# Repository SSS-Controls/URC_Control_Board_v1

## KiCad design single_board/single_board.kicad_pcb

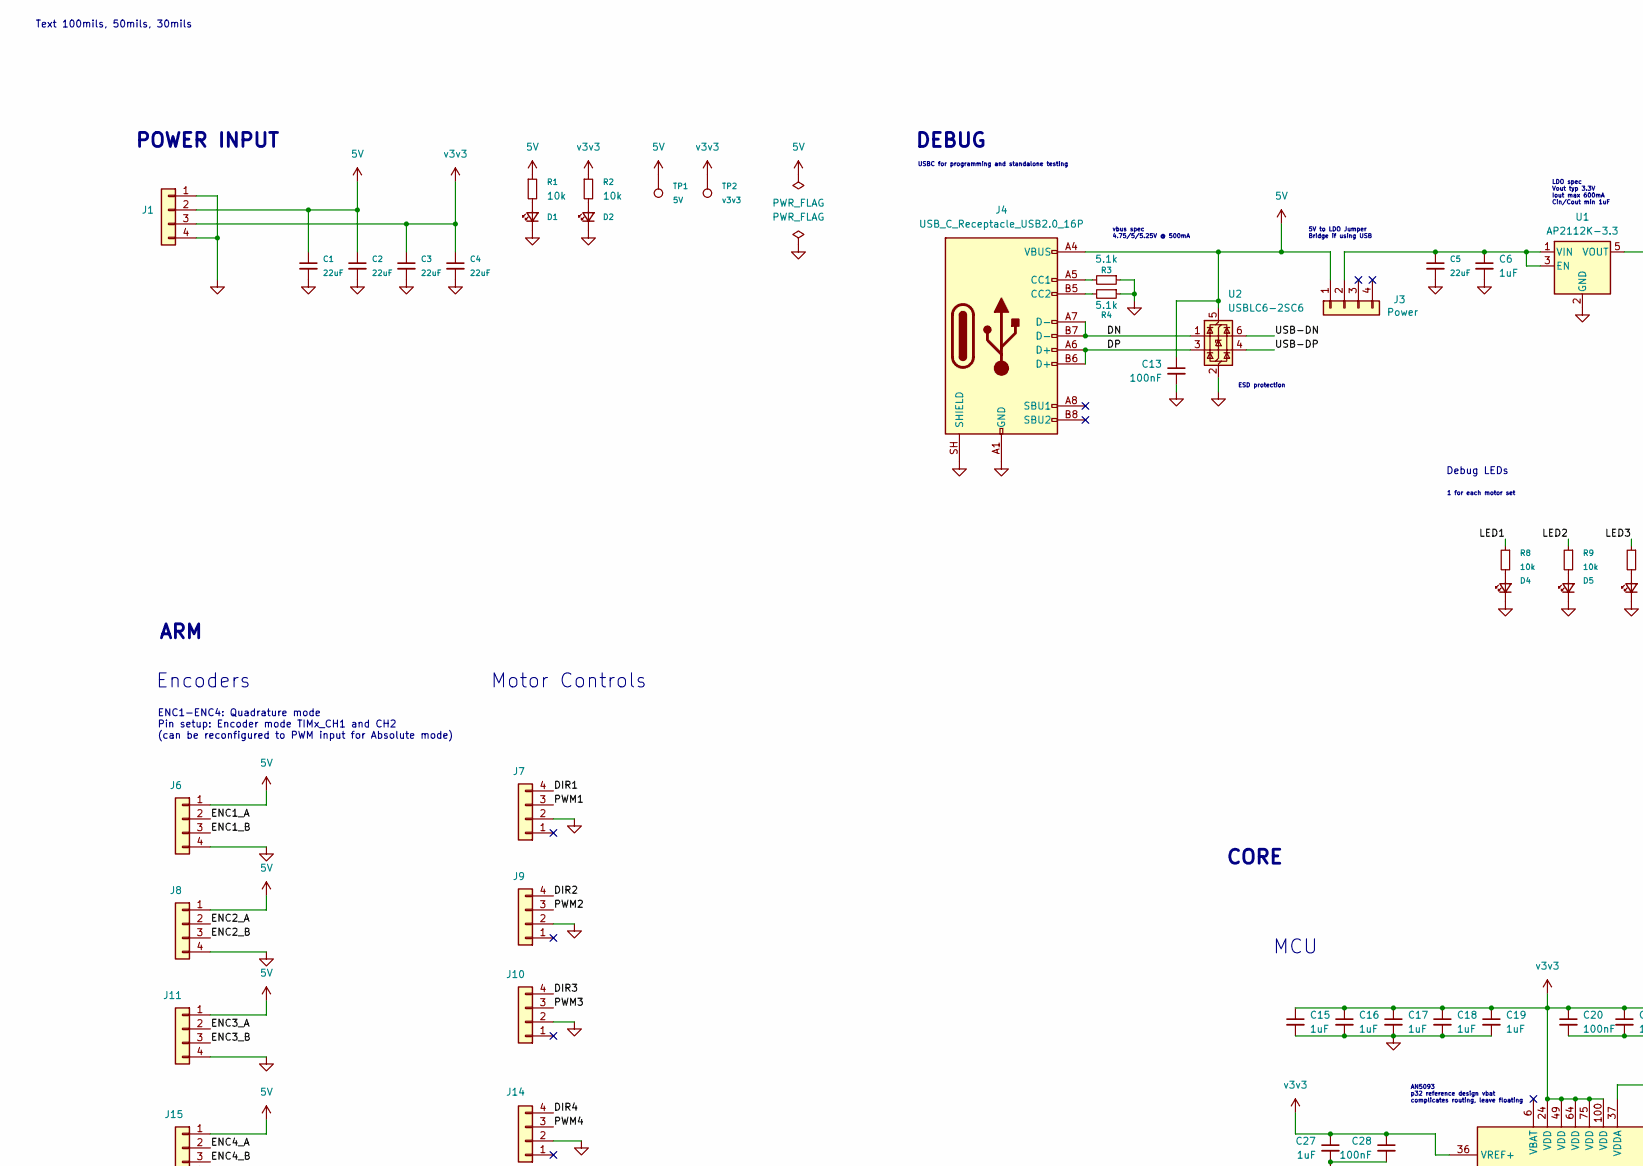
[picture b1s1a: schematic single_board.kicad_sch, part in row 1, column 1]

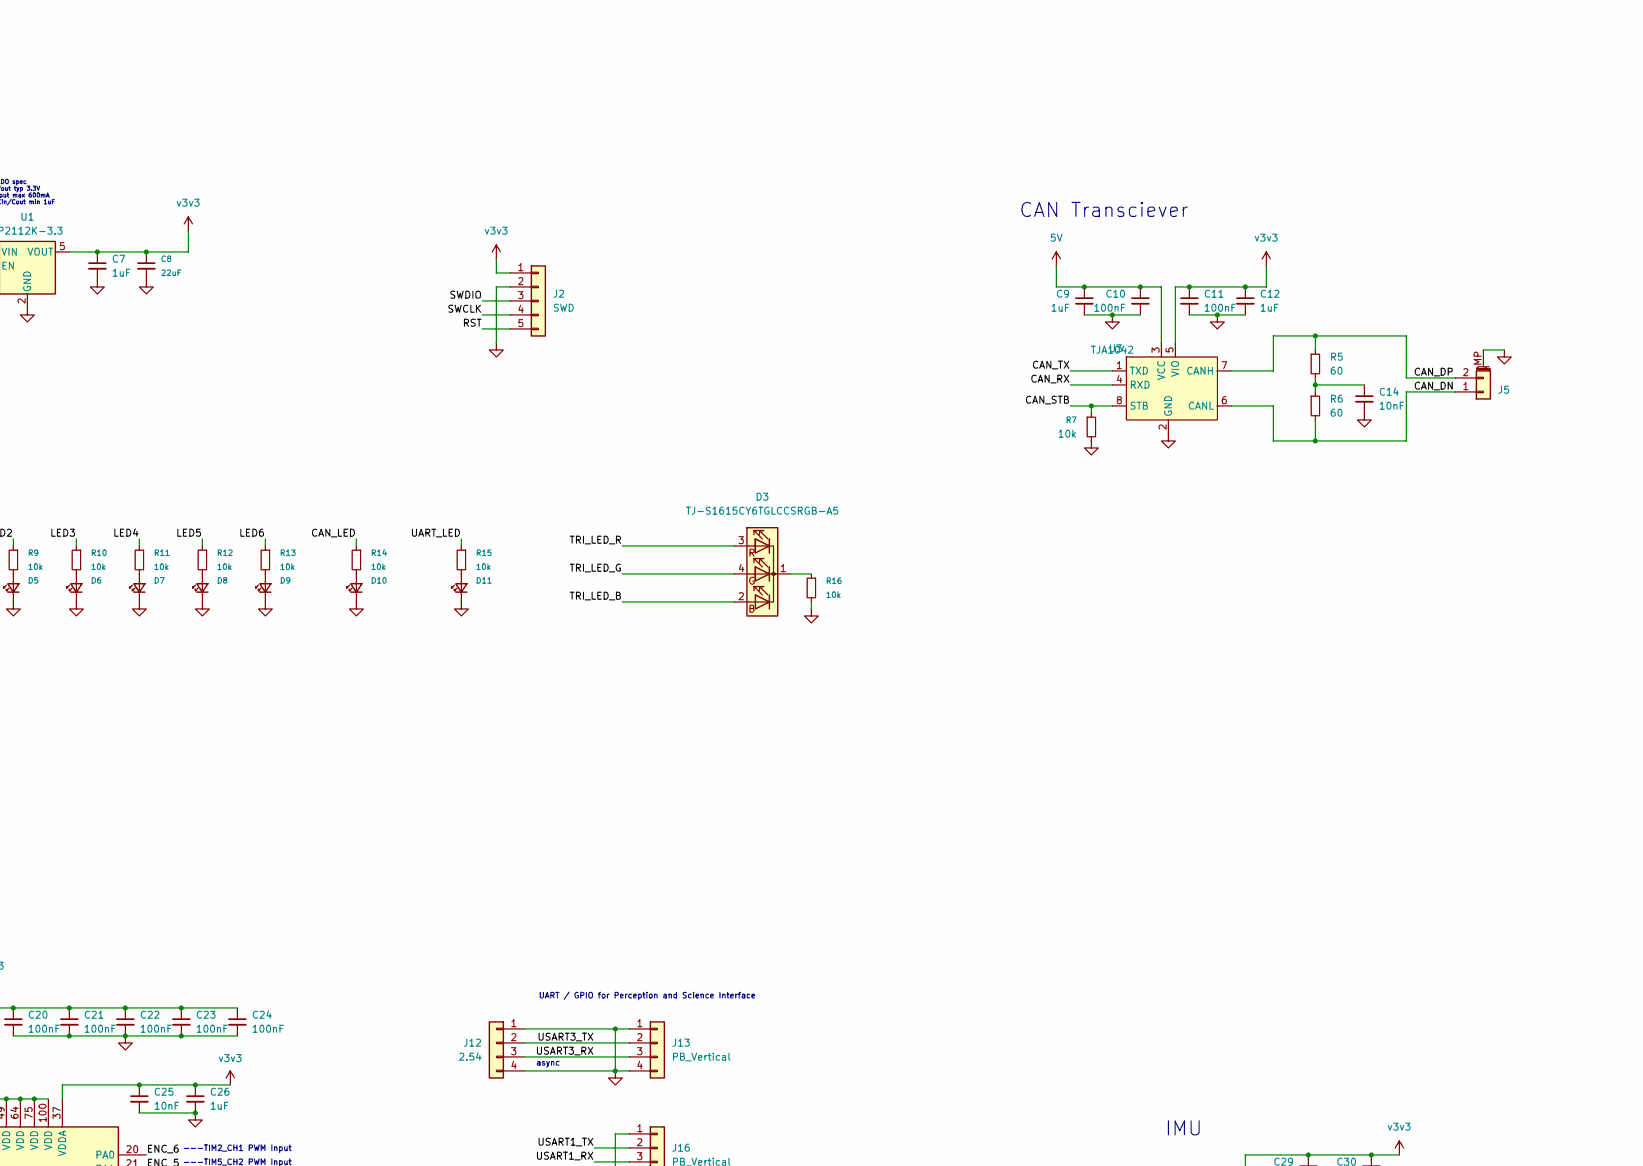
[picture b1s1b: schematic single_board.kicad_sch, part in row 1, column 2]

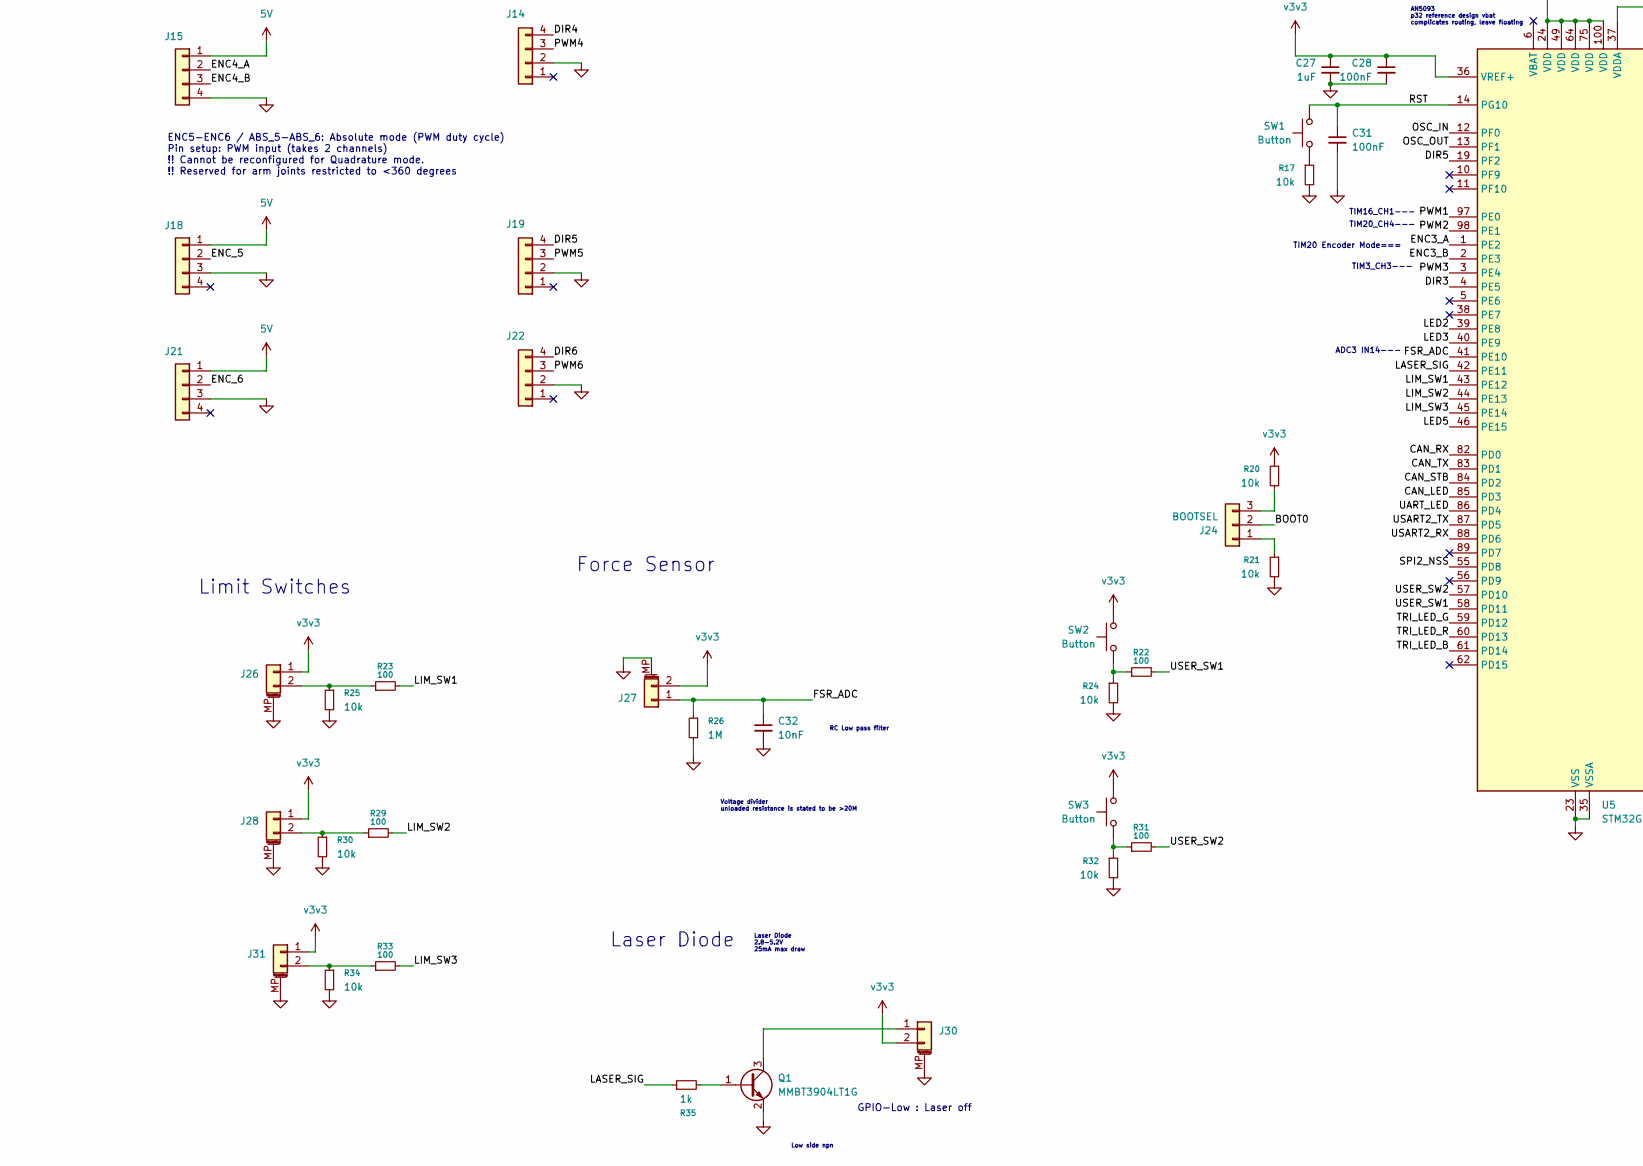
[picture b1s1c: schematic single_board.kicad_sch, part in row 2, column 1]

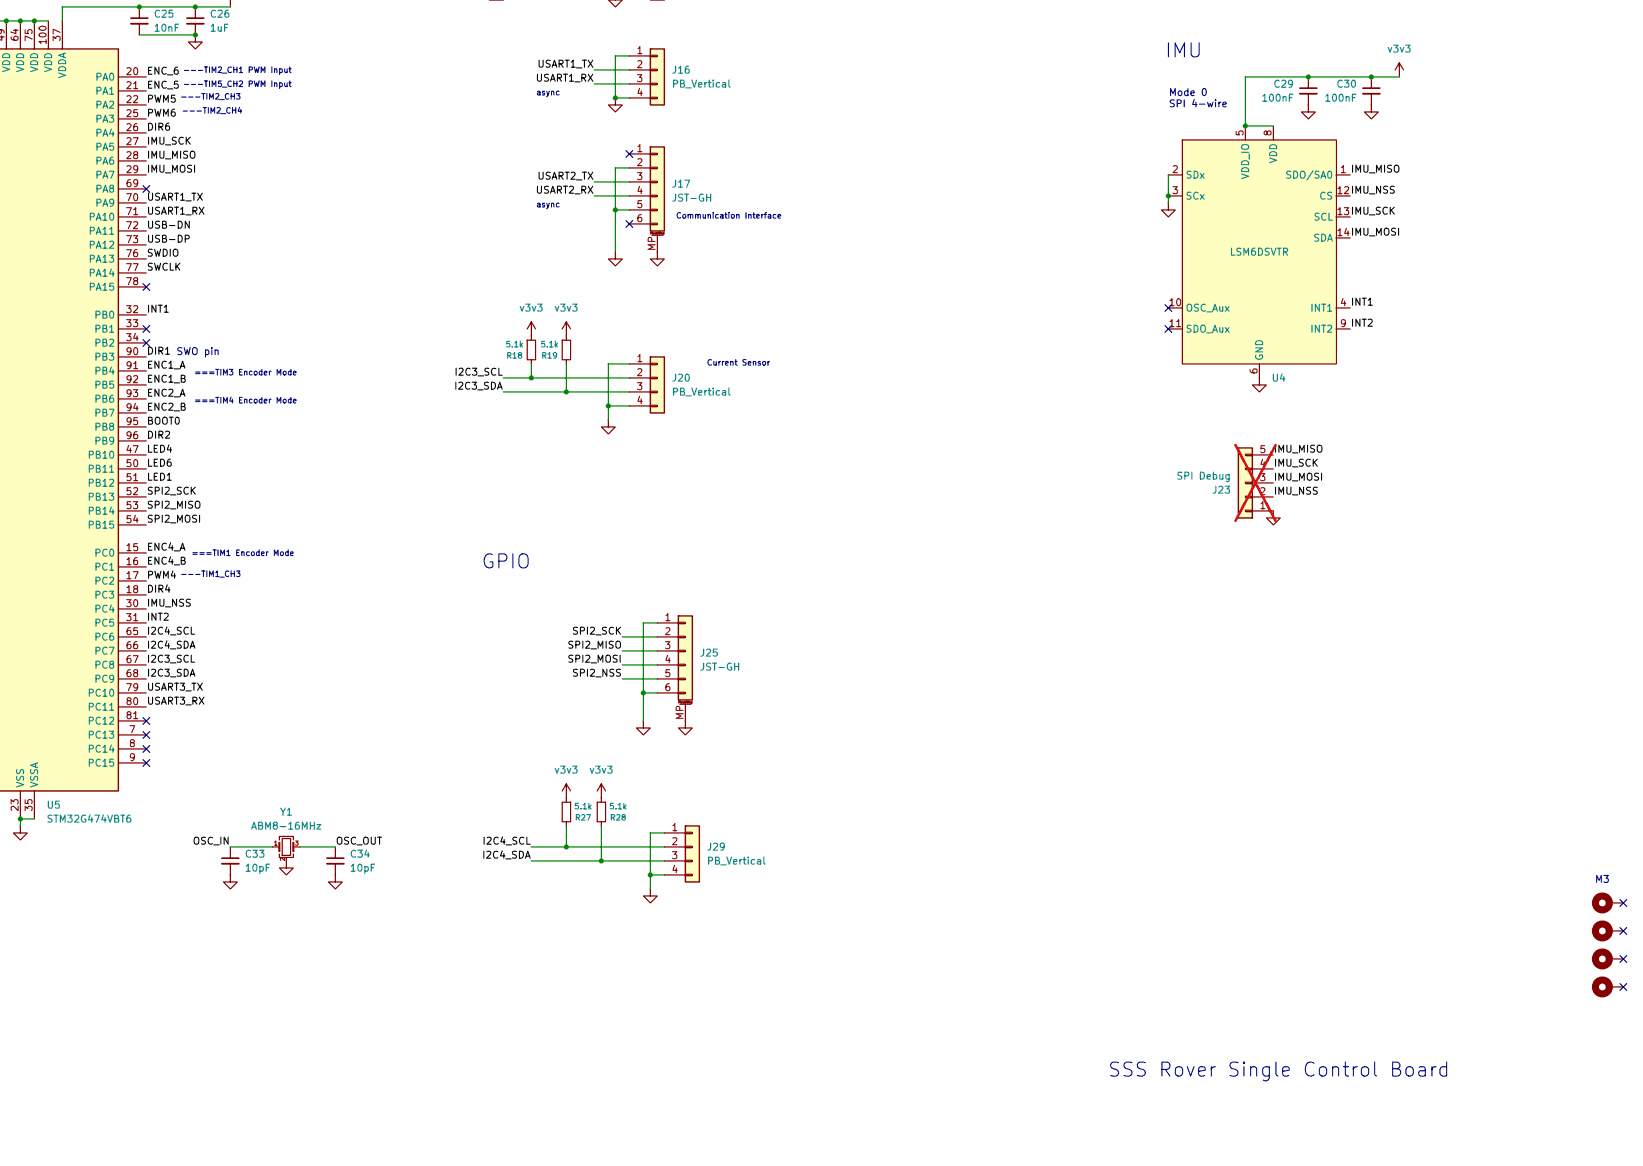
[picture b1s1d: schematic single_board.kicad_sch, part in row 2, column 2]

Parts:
C1, C2, C3, C4, C5, C8: 22uF; C_0805_2012Metric; LCSC Part # C602037
C6, C7, C9, C12, C15, C16, C17, C18, C19, C26, C27: 1uF; C_0402_1005Metric; LCSC Part # C52923
C10, C11, C13, C20, C21, C22, C23, C24, C28, C29, C30, C31: 100nF; C_0402_1005Metric; LCSC Part # C100072
C14, C25, C32: 10nF; C_0402_1005Metric; LCSC Part # C15195
C33, C34: 10pF; C_0402_1005Metric; LCSC Part # C76946
D1, D2: LED_Small; LED_0603_1608Metric; LCSC Part # C5160697
D3: TJ-S1615CY6TGLCCSRGB-A5; TOGAILED; LCSC Part # C601684
D4, D5, D6, D7, D8, D9, D10, D11: LED; LED_0603_1608Metric; LCSC Part # C5160697
H1, H2, H3, H4: M3; MountingHole_3.2mm_M3_Pad
J1, J6, J7, J8, J9, J10, J11, J13, J14, J15, J16, J18, J19, J20, J21, J22, J29: PB_Vertical; Molex_PicoBlade_53047-0410_1x04_P1.25mm_Vertical; LCSC Part # C504989
J2: SWD; PinHeader_1x05_P2.54mm_Vertical
J3: Power; PinHeader_1x04_P2.54mm_Vertical
J4: USB_C_Receptacle_USB2.0_16P; USB_C_Receptacle_HRO_TYPE-C-31-M-12; LCSC Part # C165948
J5, J26, J27, J28, J30, J31: JST_GH; JST_GH_SM02B-GHS-TB_1x02-1MP_P1.25mm_Horizontal; LCSC Part # C189893
J12: 2.54; 2.54 SMD
J17, J25: JST-GH; JST_GH_SM06B-GHS-TB_1x06-1MP_P1.25mm_Horizontal; LCSC Part # C133065
J23: SPI Debug; PinHeader_1x05_P1.27mm_Vertical; not fitted
J24: BOOTSEL; PinHeader_1x03_P2.54mm_Vertical
Q1: MMBT3904LT1G; SOT-23; LCSC Part # C81464
R1, R2, R7, R8, R9, R10, R11, R12, R13, R14, R15, R16, R17, R20, R21, R24, R25, R30, R32, R34: 10k; R_0402_1005Metric; LCSC Part # C71617
R3, R4, R18, R19, R27, R28: 5.1k; R_0402_1005Metric; LCSC Part # C105872
R5, R6: 60; R_0402_1005Metric; LCSC Part # C416565
R22, R23, R29, R31, R33: 100; R_0402_1005Metric; LCSC Part # C413063
R26: 1M; R_0402_1005Metric; LCSC Part # C26083
R35: 1k; R_0402_1005Metric
SW1, SW2, SW3: Button; SW_SPST_PTS810; LCSC Part # C221897
TP1: 5V; TestPoint_Pad_D1.5mm
TP2: v3v3; TestPoint_Pad_D1.5mm
U1: AP2112K-3.3; SOT-23-5; LCSC Part # C51118
U2: USBLC6-2SC6; SOT-23-6; LCSC Part # C7519
U3: TJA1042; SOIC-8_3.9x4.9mm_P1.27mm; LCSC Part # C53670
U4: LSM6DSVTR; LSM6DSV; LCSC Part # C5267399
U5: STM32G474VBT6; LQFP-100_14x14mm_P0.5mm; LCSC Part # C730130
Y1: ABM8-16MHz; Crystal_SMD_Abracon_ABM8G-4Pin_3.2x2.5mm; LCSC Part # C179641

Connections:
5V: C1.1, C2.1, C9.1, C10.1, C13.1, J1.2, J3.1, J4.A4 (VBUS), J4.A9 (VBUS), J4.B4 (VBUS), J4.B9 (VBUS), J6.1, J8.1, J11.1, J15.1, J18.1, J21.1, R1.1, TP1.1 (1_1), U2.5 (VBUS), U3.3 (VCC)
/BOOT0: J24.2, U5.95 (PB8)
/CAN_DN: J5.1, R6.2, U3.6 (CANL)
/CAN_DP: J5.2, R5.1, U3.7 (CANH)
/CAN_LED: R14.1, U5.85 (PD3)
/CAN_RX: U3.4 (RXD), U5.82 (PD0)
/CAN_STB: R7.1, U3.8 (STB), U5.84 (PD2)
/CAN_TX: U3.1 (TXD), U5.83 (PD1)
/DIR1: J7.4, U5.90 (PB3)
/DIR2: J9.4, U5.96 (PB9)
/DIR3: J10.4, U5.4 (PE5)
/DIR4: J14.4, U5.18 (PC3)
/DIR5: J19.4, U5.19 (PF2)
/DIR6: J22.4, U5.26 (PA4)
/DN: J4.A7 (D-), J4.B7 (D-), U2.1 (I/O1)
/DP: J4.A6 (D+), J4.B6 (D+), U2.3 (I/O2)
/ENC1_A: J6.2, U5.91 (PB4)
/ENC1_B: J6.3, U5.92 (PB5)
/ENC2_A: J8.2, U5.93 (PB6)
/ENC2_B: J8.3, U5.94 (PB7)
/ENC3_A: J11.2, U5.1 (PE2)
/ENC3_B: J11.3, U5.2 (PE3)
/ENC4_A: J15.2, U5.15 (PC0)
/ENC4_B: J15.3, U5.16 (PC1)
/ENC_5: J18.2, U5.21 (PA1)
/ENC_6: J21.2, U5.20 (PA0)
/FSR_ADC: C32.1, J27.1, R26.1, U5.41 (PE10)
/I2C3_SCL: J20.2, R18.2, U5.67 (PC8)
/I2C3_SDA: J20.3, R19.2, U5.68 (PC9)
/I2C4_SCL: J29.2, R27.2, U5.65 (PC6)
/I2C4_SDA: J29.3, R28.2, U5.66 (PC7)
/IMU_MISO: J23.5, U4.1 (SDO/SA0), U5.28 (PA6)
/IMU_MOSI: J23.3, U4.14 (SDA), U5.29 (PA7)
/IMU_NSS: J23.2, U4.12 (CS), U5.30 (PC4)
/IMU_SCK: J23.4, U4.13 (SCL), U5.27 (PA5)
/INT1: U4.4 (INT1), U5.32 (PB0)
/INT2: U4.9 (INT2), U5.31 (PC5)
/LASER_SIG: R35.1, U5.42 (PE11)
/LED1: R8.1, U5.51 (PB12)
/LED2: R9.1, U5.39 (PE8)
/LED3: R10.1, U5.40 (PE9)
/LED4: R11.1, U5.47 (PB10)
/LED5: R12.1, U5.46 (PE15)
/LED6: R13.1, U5.50 (PB11)
/LIM_SW1: R23.2, U5.43 (PE12)
/LIM_SW2: R29.2, U5.44 (PE13)
/LIM_SW3: R33.2, U5.45 (PE14)
/OSC_IN: C33.1, U5.12 (PF0), Y1.1
/OSC_OUT: C34.1, U5.13 (PF1), Y1.3
/PWM1: J7.3, U5.97 (PE0)
/PWM2: J9.3, U5.98 (PE1)
/PWM3: J10.3, U5.3 (PE4)
/PWM4: J14.3, U5.17 (PC2)
/PWM5: J19.3, U5.22 (PA2)
/PWM6: J22.3, U5.25 (PA3)
/RST: C31.1, J2.5, SW1.2, U5.14 (PG10)
/SPI2_MISO: J25.3, U5.53 (PB14)
/SPI2_MOSI: J25.4, U5.54 (PB15)
/SPI2_NSS: J25.5, U5.55 (PD8)
/SPI2_SCK: J25.2, U5.52 (PB13)
/SWCLK: J2.4, U5.77 (PA14)
/SWDIO: J2.3, U5.76 (PA13)
/TRI_LED_B: D3.2 (BA), U5.61 (PD14)
/TRI_LED_G: D3.4 (GA), U5.59 (PD12)
/TRI_LED_R: D3.3 (RA), U5.60 (PD13)
/UART_LED: R15.1, U5.86 (PD4)
/USART1_RX: J16.3, U5.71 (PA10)
/USART1_TX: J16.2, U5.70 (PA9)
/USART2_RX: J17.4, U5.88 (PD6)
/USART2_TX: J17.3, U5.87 (PD5)
/USART3_RX: J12.3, J13.3, U5.80 (PC11)
/USART3_TX: J12.2, J13.2, U5.79 (PC10)
/USB-DN: U2.6 (I/O1), U5.72 (PA11)
/USB-DP: U2.4 (I/O2), U5.73 (PA12)
/USER_SW1: R22.2, U5.58 (PD11)
/USER_SW2: R31.2, U5.57 (PD10)
GND: C1.2, C2.2, C3.2, C4.2, C5.2, C6.2, C7.2, C8.2, C9.2, C10.2, C11.2, C12.2, C13.2, C14.2, C15.2, C16.2, C17.2, C18.2, C19.2, C20.2, C21.2, C22.2, C23.2, C24.2, C25.2, C26.2, C27.2, C28.2, C29.2, C30.2, C31.2, C32.2, C33.2, C34.2, D1.1 (K), D2.1 (K), D4.1 (K), D5.1 (K), D6.1 (K), D7.1 (K), D8.1 (K), D9.1 (K), D10.1 (K), D11.1 (K), J1.1, J1.4, J2.2, J4.A1 (GND), J4.A12 (GND), J4.B1 (GND), J4.B12 (GND), J4.SH (SHIELD), J5.MP (MountPin), J6.4, J7.2, J8.4, J9.2, J10.2, J11.4, J12.1, J12.4, J13.1, J13.4, J14.2, J15.4, J16.1, J16.4, J17.2, J17.5, J17.MP (MountPin), J18.3, J19.2, J20.1, J20.4, J21.3, J22.2, J23.1, J25.1, J25.6, J25.MP (MountPin), J26.MP (MountPin), J27.MP (MountPin), J28.MP (MountPin), J29.1, J29.4, J30.MP (MountPin), J31.MP (MountPin), Q1.2 (E), R3.1, R4.1, R7.2, R16.2, R17.2, R21.2, R24.2, R25.2, R26.2, R30.2, R32.2, R34.2, U1.2 (GND), U2.2 (GND), U3.2 (GND), U4.2 (SDx), U4.3 (SCx), U4.6 (GND), U4.7 (GND), U5.23 (VSS), U5.35 (VSSA), U5.48 (VSS), U5.63 (VSS), U5.74 (VSS), U5.99 (VSS), Y1.2 (G), Y1.4 (G)
unnamed: C14.1, R5.2, R6.1
unnamed: D1.2 (A), R1.2
unnamed: D2.2 (A), R2.2
unnamed: D3.1 (K), R16.1
unnamed: D4.2 (A), R8.2
unnamed: D5.2 (A), R9.2
unnamed: D6.2 (A), R10.2
unnamed: D7.2 (A), R11.2
unnamed: D8.2 (A), R12.2
unnamed: D9.2 (A), R13.2
unnamed: D10.2 (A), R14.2
unnamed: D11.2 (A), R15.2
unnamed: C5.1, C6.1, J3.2, U1.1 (VIN), U1.3 (EN)
unnamed: J4.A5 (CC1), R3.2
unnamed: J4.B5 (CC2), R4.2
unnamed: J24.1, R21.1
unnamed: J24.3, R20.2
unnamed: J26.2, R23.1, R25.1
unnamed: J28.2, R29.1, R30.1
unnamed: J30.1, Q1.3 (C)
unnamed: J31.2, R33.1, R34.1
unnamed: Q1.1 (B), R35.2
unnamed: R17.1, SW1.1
unnamed: R22.1, R24.1, SW2.1
unnamed: R31.1, R32.1, SW3.1
v3v3: C3.1, C4.1, C7.1, C8.1, C11.1, C12.1, C15.1, C16.1, C17.1, C18.1, C19.1, C20.1, C21.1, C22.1, C23.1, C24.1, C25.1, C26.1, C27.1, C28.1, C29.1, C30.1, J1.3, J2.1, J26.1, J27.2, J28.1, J30.2, J31.1, R2.1, R18.1, R19.1, R20.1, R27.1, R28.1, SW2.2, SW3.2, TP2.1 (1_1), U1.5 (VOUT), U3.5 (VIO), U4.5 (VDD_IO), U4.8 (VDD), U5.24 (VDD), U5.36 (VREF+), U5.37 (VDDA), U5.49 (VDD), U5.64 (VDD), U5.75 (VDD), U5.100 (VDD)

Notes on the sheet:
---TIM2_CH4
Mode 0 SPI 4-wire
Voltage divider unloaded resistance is stated to be >20M
ENC1-ENC4: Quadrature mode Pin setup: Encoder mode TIMx_CH1 and CH2 (can be reconfigured to PWM input for Absolute mode)
1 for each motor set
Text 100mils, 50mils, 30mils
SSS Rover Single Control Board
Low side npn
GPIO-Low : Laser off
===TIM4 Encoder Mode
IMU
UART / GPIO for Perception and Science Interface
TIM3_CH3---
AN5093 p32 reference design vbat complicates routing, leave floating
Limit Switches
POWER INPUT
Laser Diode 2.8-5.2V 25mA max draw
MCU
Debug LEDs
async
5V to LDO Jumper Bridge if using USB
TIM20_CH4---
ESD protection
Communication Interface
RC Low pass filter
---TIM2_CH3
SWO pin
Encoders
ENC5-ENC6 / ABS_5-ABS_6: Absolute mode (PWM duty cycle) Pin setup: PWM input (takes 2 channels) !! Cannot be reconfigured for Quadrature mode. !! Reserved for arm joints restricted to <360 degrees
---TIM2_CH1 PWM Input
DEBUG
LDO spec Vout typ 3.3V Iout max 600mA Cin/Cout min 1uF
Current Sensor
ARM
USBC for programming and standalone testing
===TIM3 Encoder Mode
GPIO
TIM20 Encoder Mode===
vbus spec 4.75/5/5.25V @ 500mA
Laser Diode

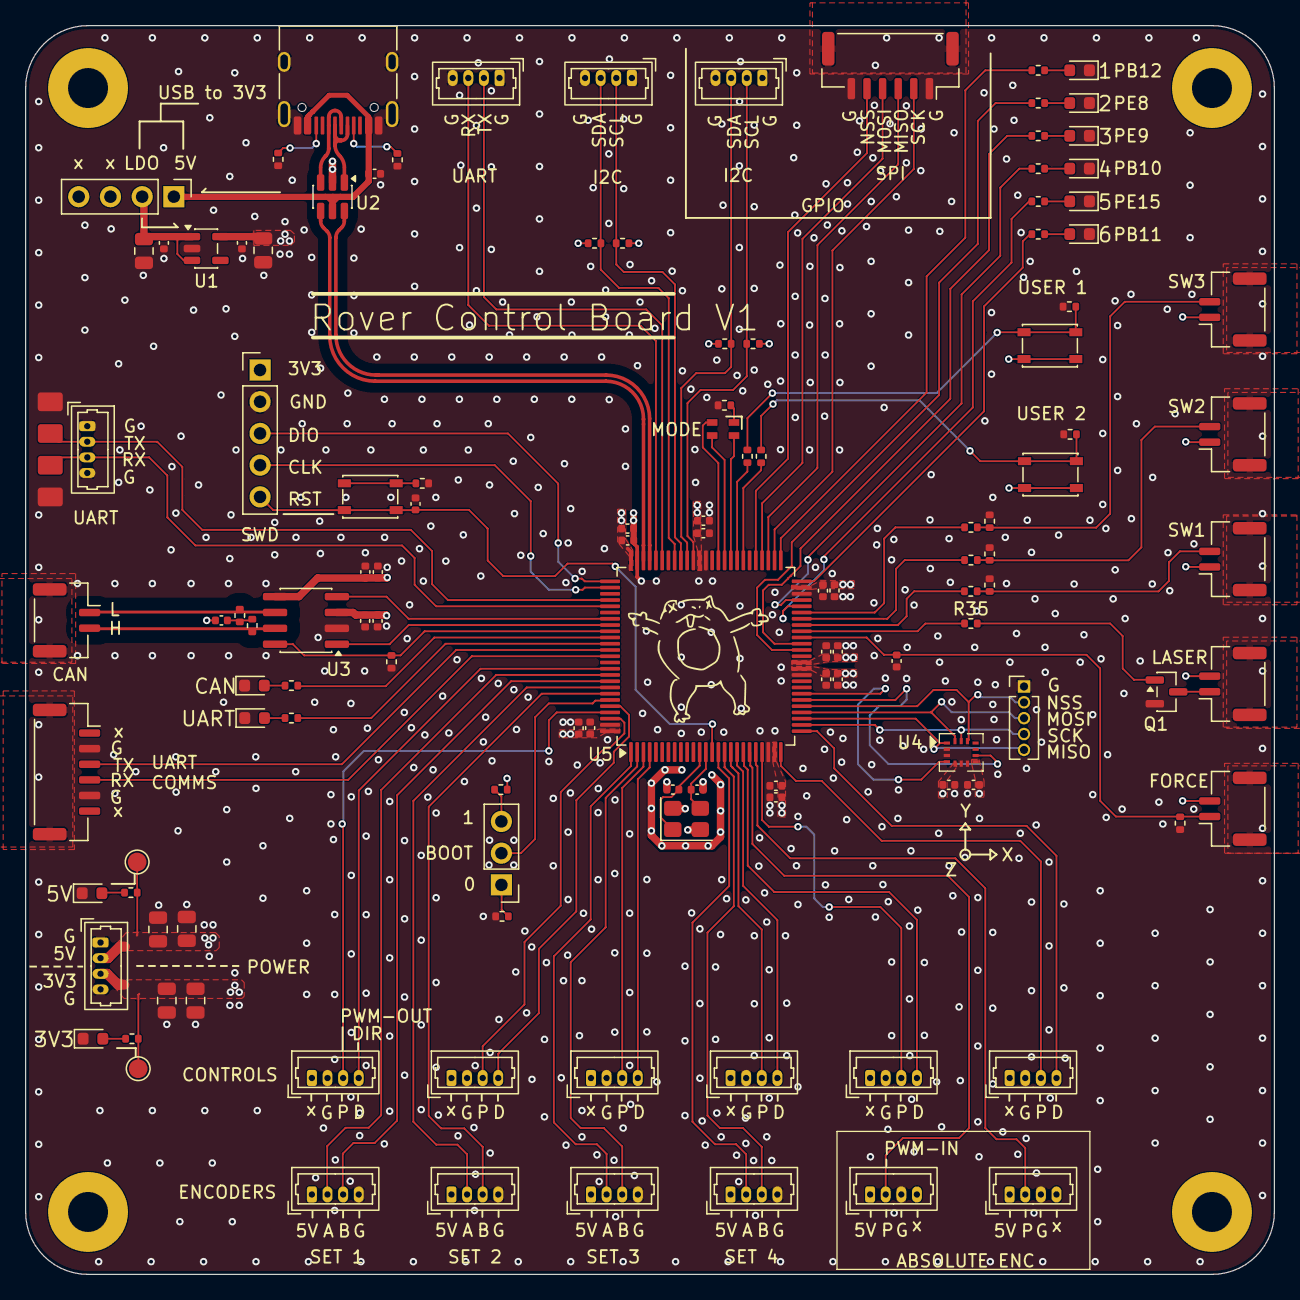
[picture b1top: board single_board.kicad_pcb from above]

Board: 4 copper layers, 100.0 x 100.0 mm, 127 parts (0 on the bottom side), 103 nets.
